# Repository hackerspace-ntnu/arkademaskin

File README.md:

# arcade-piano
An arcade machine based on a piano.

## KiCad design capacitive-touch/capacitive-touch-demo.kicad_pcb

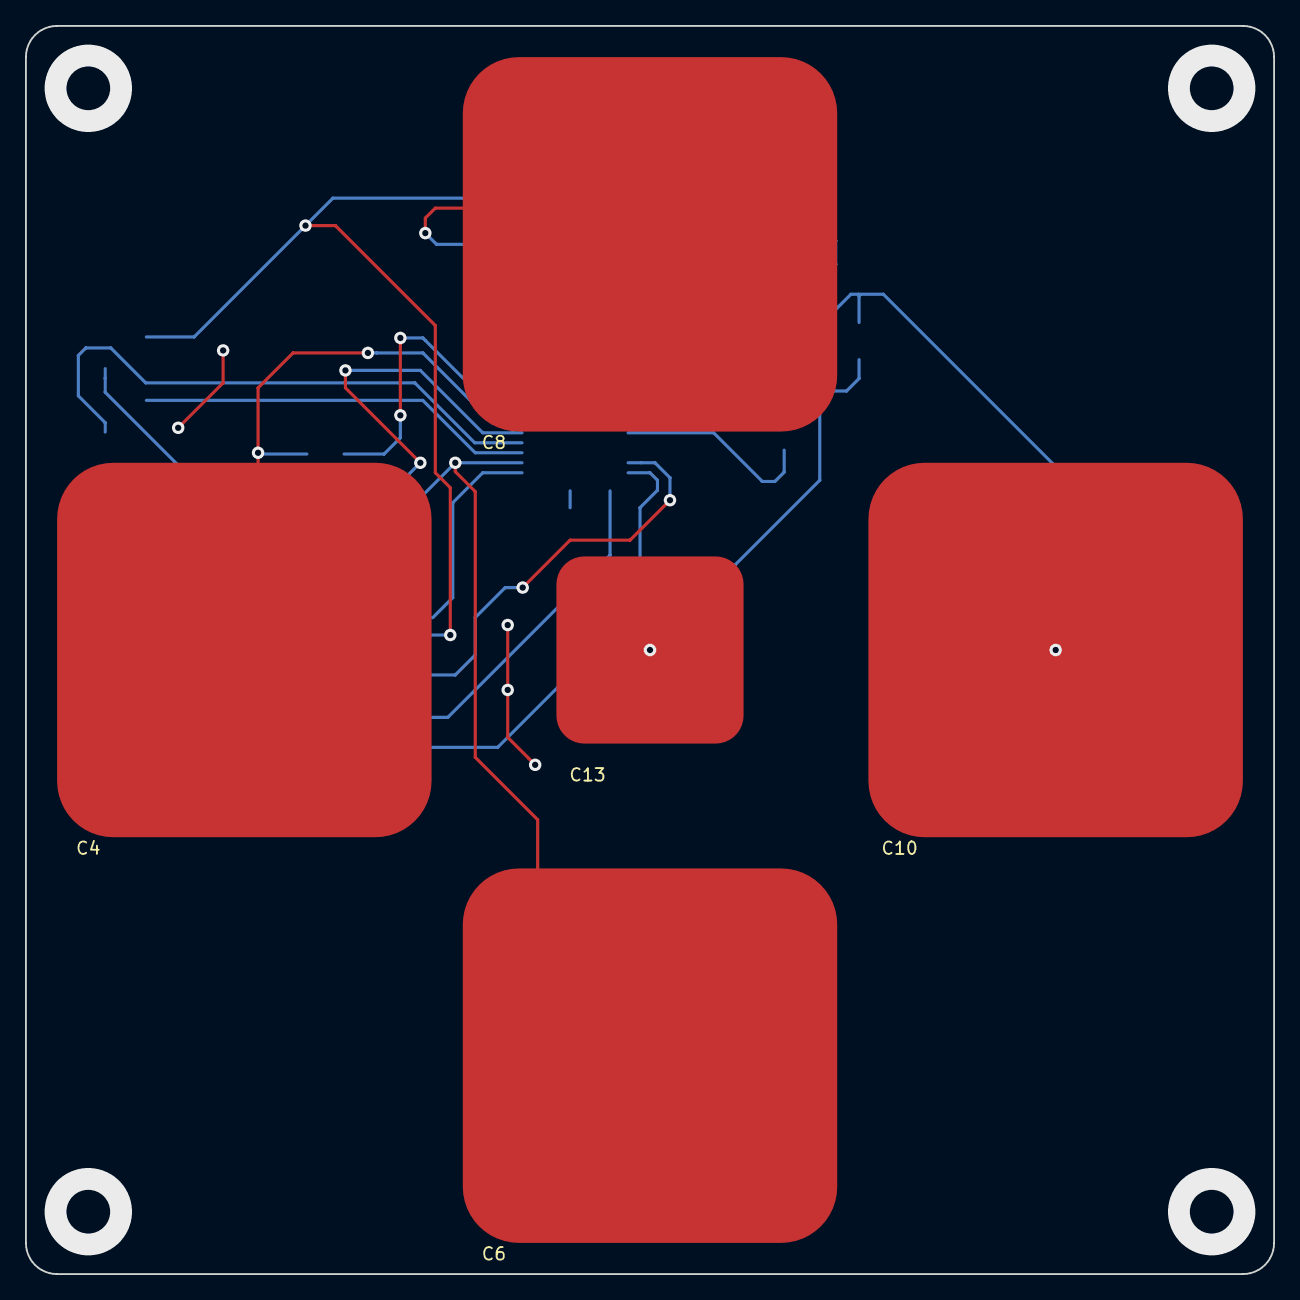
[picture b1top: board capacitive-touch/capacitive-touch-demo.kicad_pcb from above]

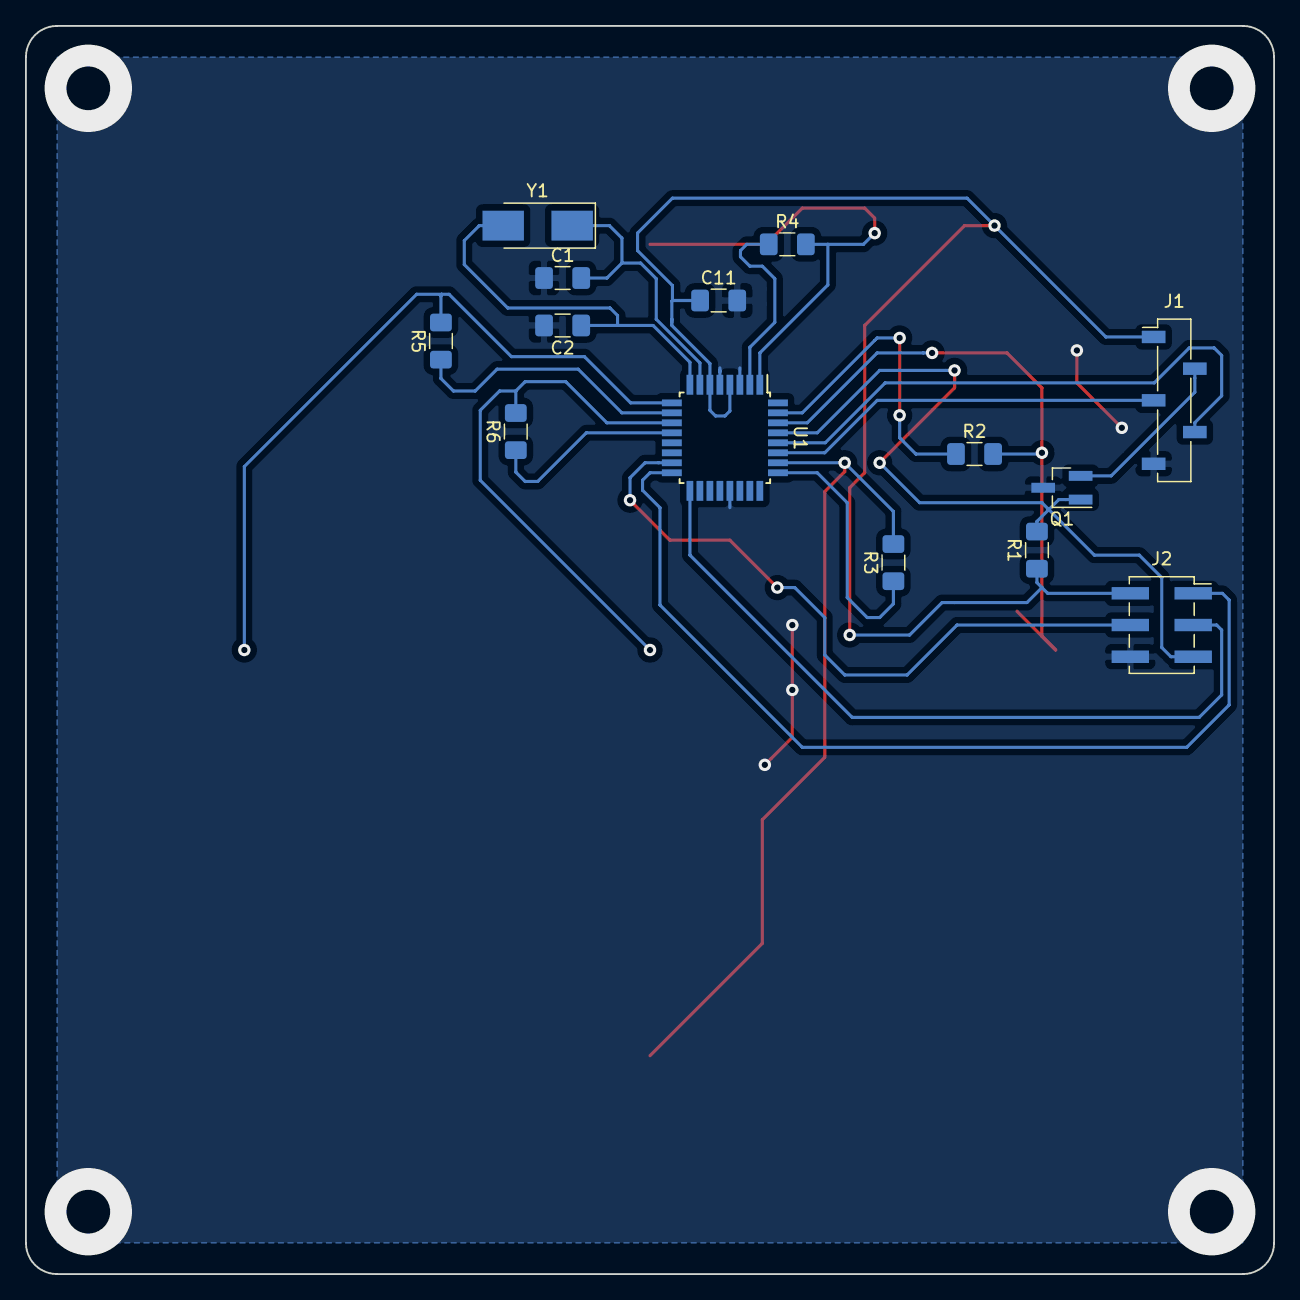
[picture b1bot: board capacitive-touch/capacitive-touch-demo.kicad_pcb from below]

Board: 2 copper layers, 100.0 x 100.0 mm, 19 parts (14 on the bottom side), 21 nets.

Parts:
C1, C2: 20pF; C_1206_3216Metric_Pad1.42x1.75mm_HandSolder
C4, C6, C8, C10: capacitive-pad
C11: 1n; C_1206_3216Metric_Pad1.42x1.75mm_HandSolder
C13: capacitive-pad; capacitive-pad-small
J1: Conn_01x05_Male; PinSocket_1x05_P2.54mm_Vertical_SMD_Pin1Left
J2: AVR-ISP-6; PinSocket_2x03_P2.54mm_Vertical_SMD
Q1: BS170; SOT-23_Handsoldering
R1: 10k; R_1206_3216Metric_Pad1.42x1.75mm_HandSolder
R2, R3, R4, R5, R6: 1M; R_1206_3216Metric_Pad1.42x1.75mm_HandSolder
U1: ATmega168-20AU; TQFP-32_7x7mm_P0.8mm
Y1: 16MHz; Crystal_SMD_Abracon_ABM3-2Pin_5.0x3.2mm_HandSoldering

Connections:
/MISO: J2.1, U1.16
/MOSI: J2.4, U1.15
/RPin: J2.5, Q1.1, R1.2, U1.29
/SCK: J2.3, U1.17
/SCL: J1.4, U1.28
/SDA: J1.3, U1.27
/clk1: C1.2, U1.7, Y1.1
/clk2: C2.2, U1.8, Y1.2
GND: C1.1, C2.1, C11.2, J1.5, J2.6, Q1.3, U1.3, U1.5, U1.21
unnamed: C4.1, R2.2, U1.30
unnamed: C6.1, R3.2, U1.26
unnamed: C8.1, R4.2, U1.1
unnamed: C10.1, R5.2, U1.9
unnamed: C13.1, R6.2, U1.11
unnamed: J1.2, Q1.2
unnamed: R2.1, U1.31
unnamed: R3.1, U1.25
unnamed: R4.1, U1.2
unnamed: R5.1, U1.10
unnamed: R6.1, U1.12
VCC: C11.1, J1.1, J2.2, R1.1, U1.4, U1.6

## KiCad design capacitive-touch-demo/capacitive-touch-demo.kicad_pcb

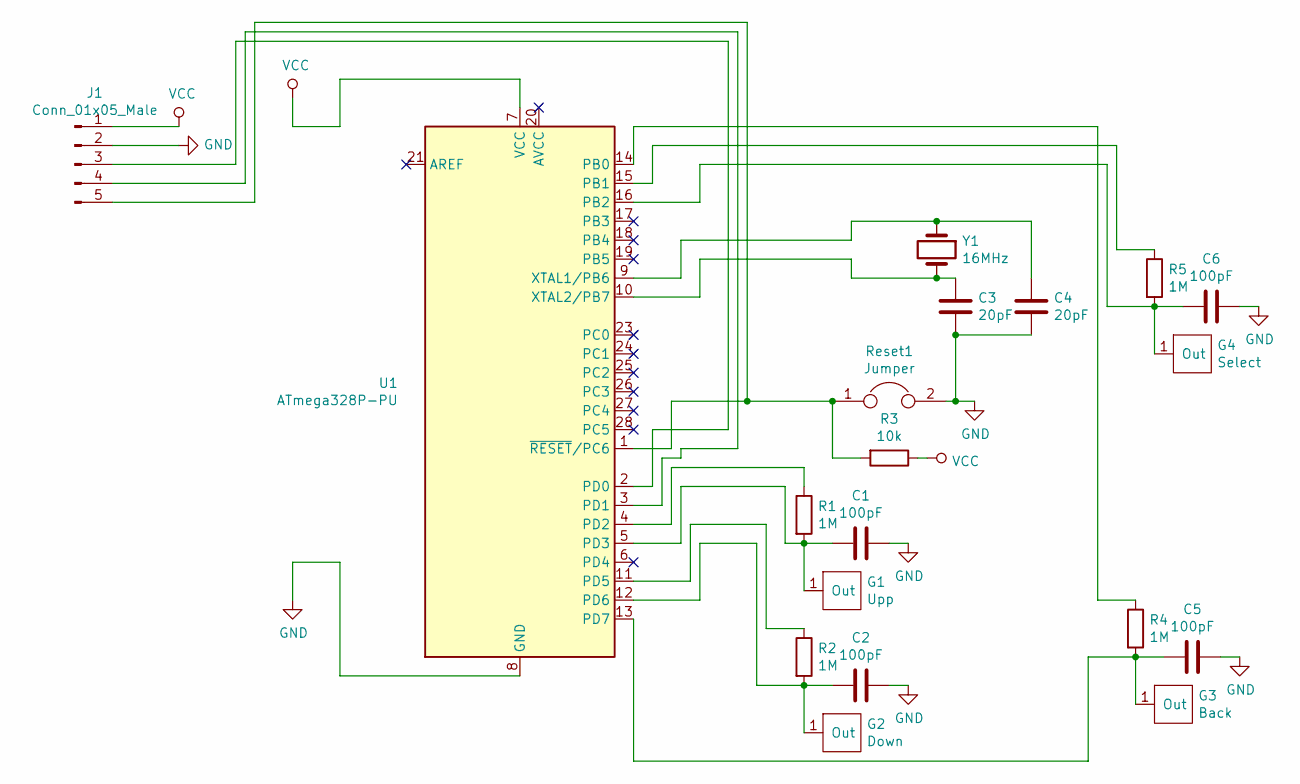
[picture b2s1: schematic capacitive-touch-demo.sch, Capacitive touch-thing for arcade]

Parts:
C1, C2, C5, C6: 100pF; C_Axial_L3.8mm_D2.6mm_P7.50mm_Horizontal
C3, C4: 20pF; C_Axial_L3.8mm_D2.6mm_P7.50mm_Horizontal
G1: Upp; pads-cap
G2: Down; pads-cap
G3: Back; pads-cap
G4: Select; pads-cap
J1: Conn_01x05_Male; Harwin_M20-89005xx_1x05_P2.54mm_Horizontal
R1, R2, R4, R5: 1M; R_Axial_DIN0204_L3.6mm_D1.6mm_P5.08mm_Horizontal
R3: 10k; R_Axial_DIN0204_L3.6mm_D1.6mm_P5.08mm_Horizontal
Reset1: Jumper; SolderJumper-2_P1.3mm_Open_Pad1.0x1.5mm
U1: ATmega328P-PU; DIP-28_W7.62mm
Y1: 16MHz; Crystal_HC18-U_Horizontal

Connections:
GND: C1.2, C2.2, C3.2, C4.2, C5.2, C6.2, J1.2, Reset1.2, U1.8 (GND), U1.22 (GND)
unnamed: C1.1, G1.1, R1.2, U1.5 (PD3)
unnamed: C2.1, G2.1, R2.2, U1.12 (PD6)
unnamed: C3.1, U1.10 (XTAL2/PB7), Y1.2
unnamed: C4.1, U1.9 (XTAL1/PB6), Y1.1
unnamed: C5.1, G3.1, R4.2, U1.13 (PD7)
unnamed: C6.1, G4.1, R5.2, U1.16 (PB2)
unnamed: J1.3, U1.2 (PD0)
unnamed: J1.4, U1.3 (PD1)
unnamed: J1.5, R3.2, Reset1.1, U1.1 (~RESET~/PC6)
unnamed: R1.1, U1.4 (PD2)
unnamed: R2.1, U1.11 (PD5)
unnamed: R4.1, U1.14 (PB0)
unnamed: R5.1, U1.15 (PB1)
VCC: J1.1, R3.1, U1.7 (VCC)

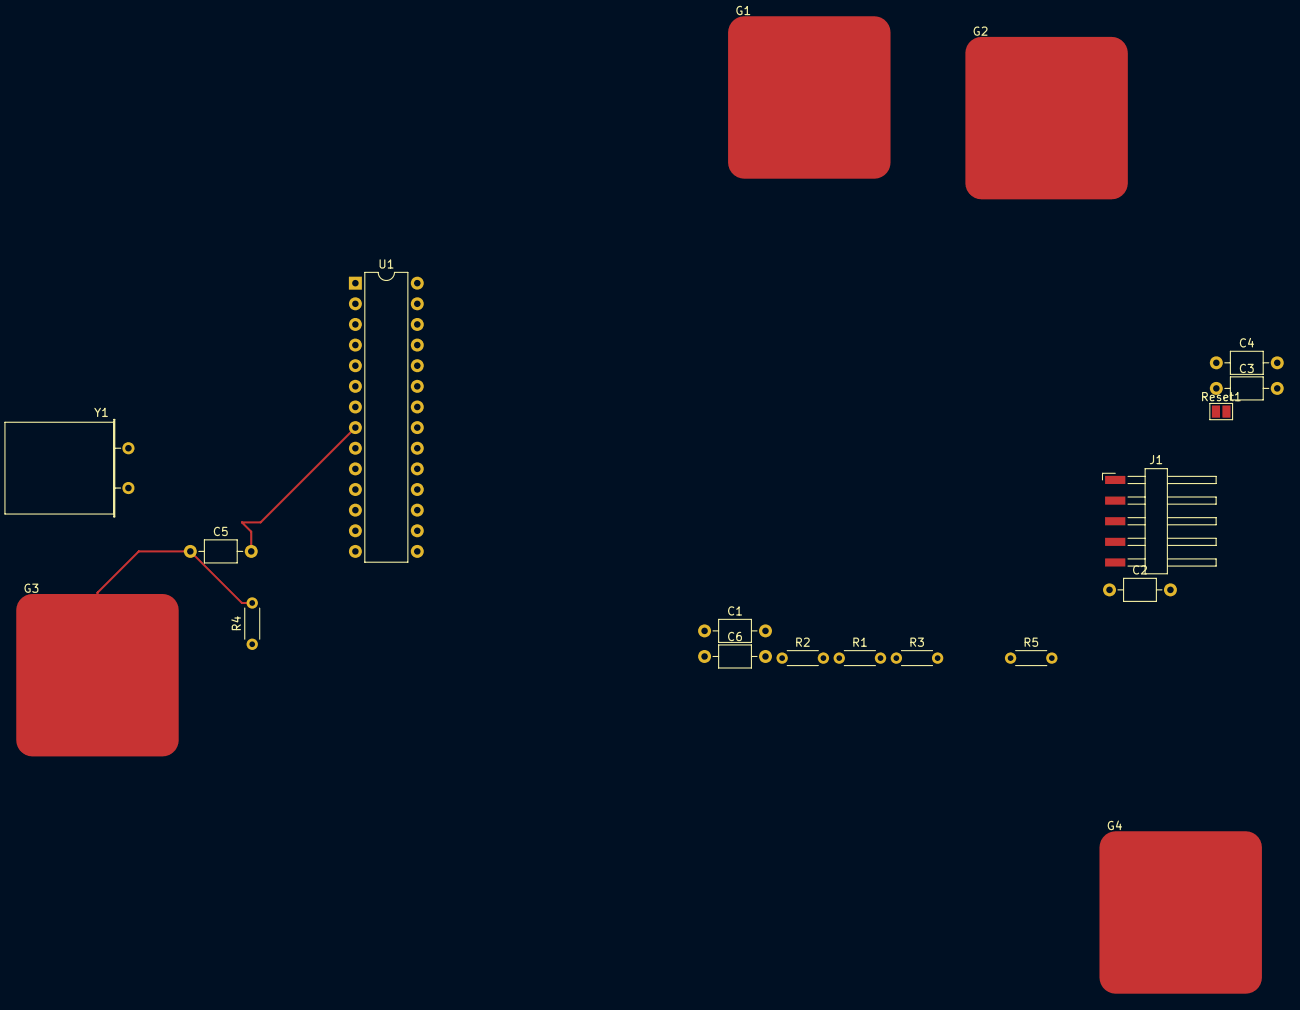
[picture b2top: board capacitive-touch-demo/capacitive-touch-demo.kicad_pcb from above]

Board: 2 copper layers, 19 parts (0 on the bottom side), 15 nets.

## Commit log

2018-10-22 Initial commit for expansions
2018-11-09 Arbeidskveld, laget mye av standaren for expansions.
2018-11-23 Started making pcbs
2018-12-07 Did some work on the capacative touch schematics
2018-12-07 Fixed paths to libraries for schematics
2018-12-08 Addet to .gitignore to support UNITY-projects
2019-01-22 La til nåværende piano-pong-spill
2019-02-07 Tester å benytte graphviz istedenfor dia til grafer
2019-02-26 Ting til pcb
2019-02-28 Rerutet og oppdaterte fotavtrykk på pcb til kapacativ touch
2019-03-05 Prepared for change from unity to godot
2019-03-05 CAD...
    FINALLY
2019-03-09 Fikset på kretskort
2019-09-25 Ting fra før sommeren???
2019-09-26 Oppdatert ekspansjonskort spesifikasjon
2019-09-26 Oppdatert spesifikasjon
2019-10-03 Power wiring proposal, added diagram
2019-10-03 Audio wiring proposal, added diagram
2019-10-03 Updated Molex current info
2019-10-03 Updated to correct PNG
2019-10-22 La til (blant annet) kretsskjema for alt
2019-10-23 Fiksel litt i tegningen
2019-10-23 Added shell scripts for supporting flash games and custom resutions.
2019-10-28 Add more robust resolution handler
2019-10-28 Add Boxhead 2Play Rooms startup script
2019-10-30 Add submodule test
2020-01-20 kodi init fil
2020-02-11 Update spesifikasjon.org
    Lagt til detection pin i spec.
2020-03-02 Et eksempel på en post request som kan sendes til kodi
2020-03-06 added the possiblity of sending e popup post request to kodi
2020-03-06 added post request for rebooting system that hosts kodi, and quiting kodi application
2020-03-09 added code for opening plugin
2020-03-09 now the post request til directly take you to the plugin
2020-10-03 updated kodi python script
2020-10-17 Touchpad sending capasctive touch values
2020-10-17 added more rpc requests
2020-10-22 added backing function to python script
2020-11-21 Send arrow key commands
2021-03-14 keyboard input script
    using bits, 1=f13, 0=f14, for every 8 bitstring the string will become empty
2021-03-21 readme file for scripts
2021-03-21 dir json file
2021-04-18 new keyboard reader for forwarding controller inputs

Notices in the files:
capacitive-touch-demo/capacitive-touch-demo.sch:
MIT licence applies
